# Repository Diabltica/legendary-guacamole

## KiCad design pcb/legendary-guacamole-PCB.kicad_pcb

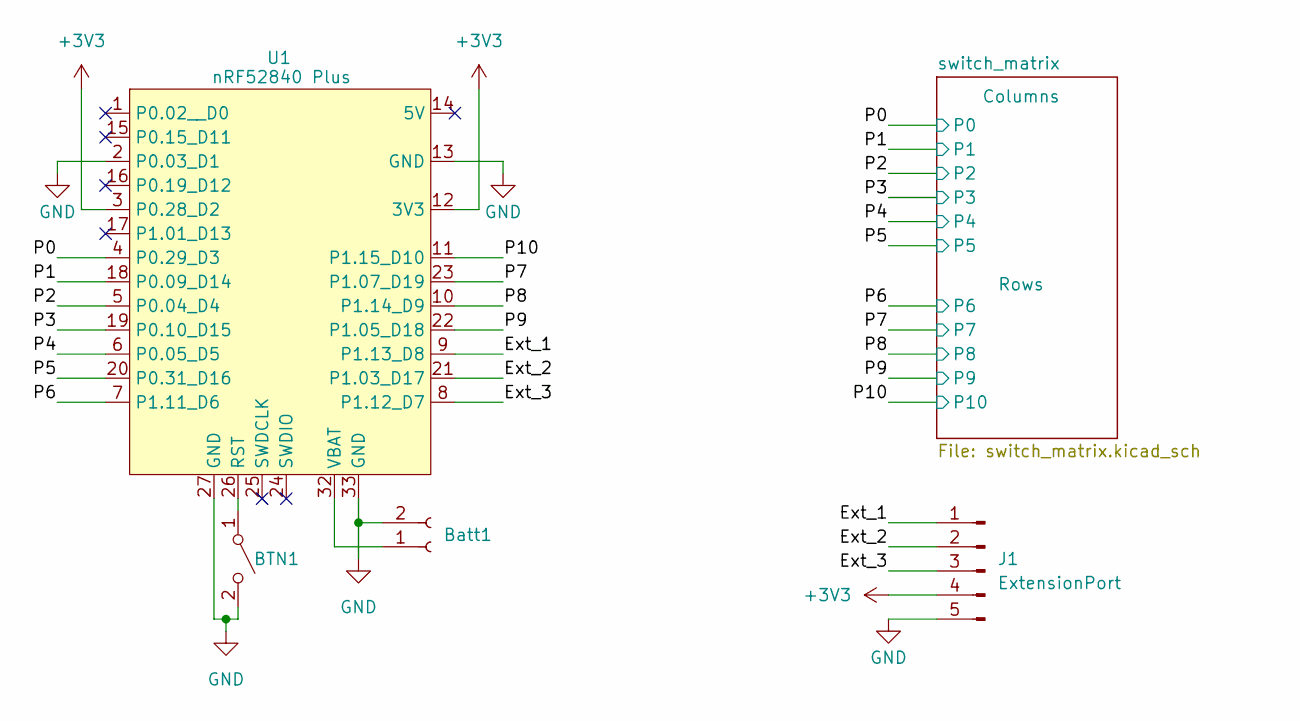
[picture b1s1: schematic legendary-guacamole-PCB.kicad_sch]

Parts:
BTN1: EVPBT5A4A000
Batt1: battery_connector_jst_ph_2
J1: ExtensionPort; PinHeader_1x05_P2.54mm_Vertical
U1: nRF52840 Plus; XIAO-nRF52840-Plus-SMD

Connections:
+3V3: J1.4, U1.3 (P0.28_D2), U1.12 (3V3); also elsewhere on the board
/Ext_1: J1.1, U1.9 (P1.13_D8); also elsewhere on the board
/Ext_2: J1.2, U1.21 (P1.03_D17); also elsewhere on the board
/Ext_3: J1.3, U1.8 (P1.12_D7); also elsewhere on the board
BAT_P: Batt1.1, U1.32 (VBAT); also elsewhere on the board
GND: BTN1.2 (B), Batt1.2, J1.5, U1.2 (P0.03_D1), U1.13 (GND), U1.27 (GND), U1.33 (GND); also elsewhere on the board
unnamed 8: BTN1.1 (A), U1.26 (RST); also elsewhere on the board
P0: U1.4 (P0.29_D3); also elsewhere on the board
P1: U1.18 (P0.09_D14); also elsewhere on the board
P2: U1.5 (P0.04_D4); also elsewhere on the board
P3: U1.19 (P0.10_D15); also elsewhere on the board
P4: U1.6 (P0.05_D5); also elsewhere on the board
P5: U1.20 (P0.31_D16); also elsewhere on the board
P6: U1.7 (P1.11_D6); also elsewhere on the board
P7: U1.23 (P1.07_D19); also elsewhere on the board
P8: U1.10 (P1.14_D9); also elsewhere on the board
P9: U1.22 (P1.05_D18); also elsewhere on the board
P10: U1.11 (P1.15_D10); also elsewhere on the board

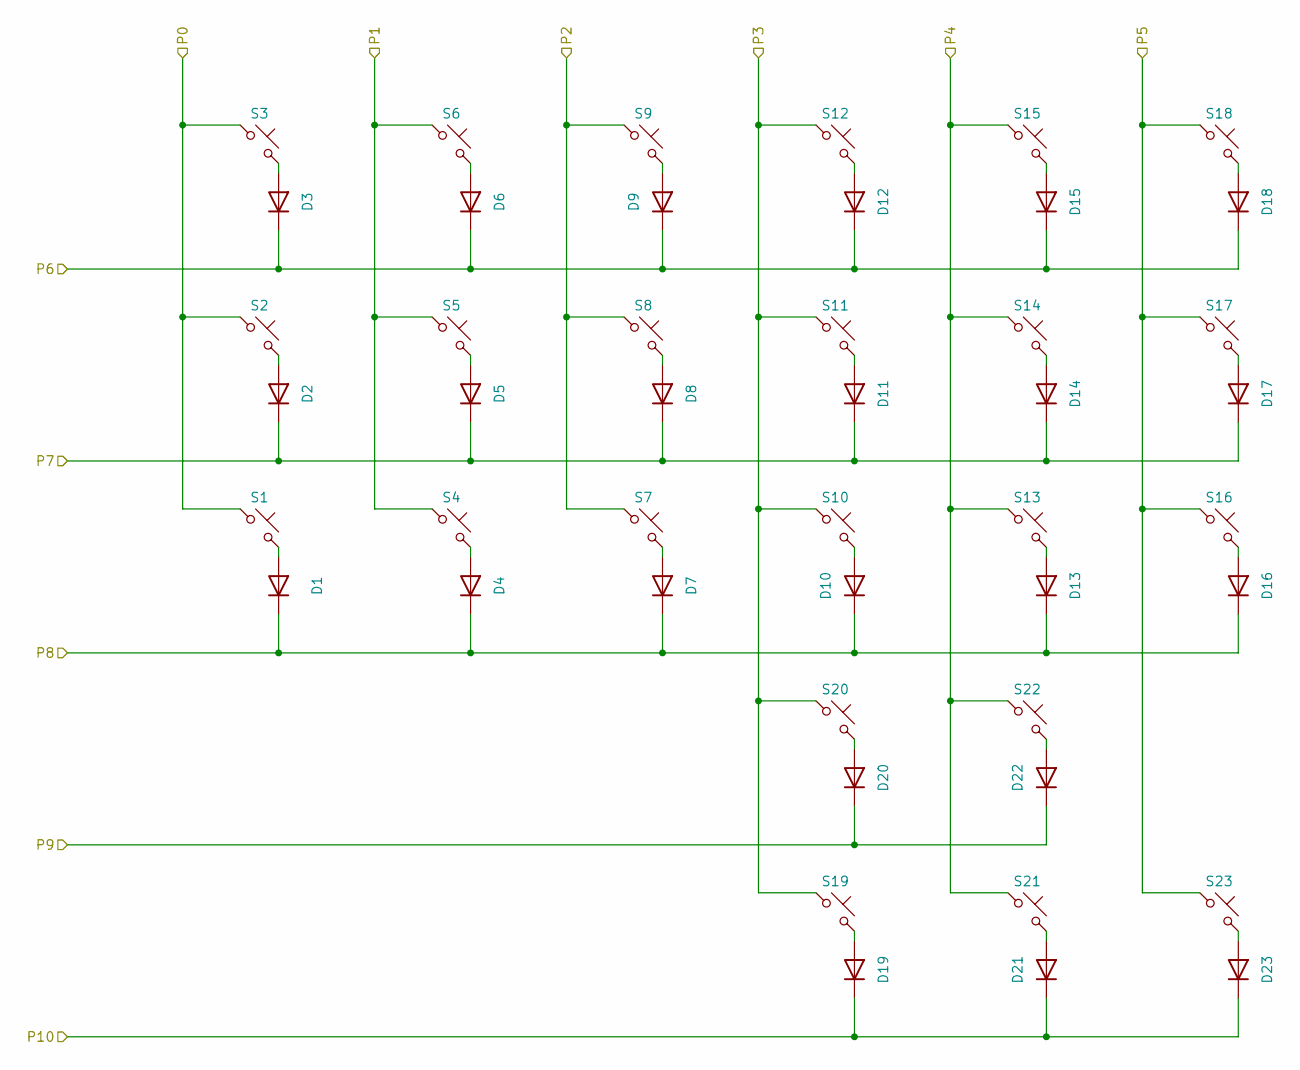
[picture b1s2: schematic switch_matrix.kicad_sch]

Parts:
D1, D2, D3, D4, D5, D6, D7, D8, D9, D10, D11, D12, D13, D14, D15, D16, D17, D18, D19, D20, D21, D22, D23: D_SOD-123
S1, S2, S3, S4, S5, S6, S7, S8, S9, S10, S11, S12, S13, S14, S15, S16, S17, S18, S19, S20, S21, S22, S23: (no value)

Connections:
P0: S1.1, S2.1, S3.1; also elsewhere on the board
P1: S4.1, S5.1, S6.1; also elsewhere on the board
P2: S7.1, S8.1, S9.1; also elsewhere on the board
P3: S10.1, S11.1, S12.1, S19.1, S20.1; also elsewhere on the board
P4: S13.1, S14.1, S15.1, S21.1, S22.1; also elsewhere on the board
P5: S16.1, S17.1, S18.1, S23.1; also elsewhere on the board
P6: D3.1 (K), D6.1 (K), D9.1 (K), D12.1 (K), D15.1 (K), D18.1 (K); also elsewhere on the board
P7: D2.1 (K), D5.1 (K), D8.1 (K), D11.1 (K), D14.1 (K), D17.1 (K); also elsewhere on the board
P8: D1.1 (K), D4.1 (K), D7.1 (K), D10.1 (K), D13.1 (K), D16.1 (K); also elsewhere on the board
P9: D20.1 (K), D22.1 (K); also elsewhere on the board
P10: D19.1 (K), D21.1 (K), D23.1 (K); also elsewhere on the board
index_bottom: D13.2 (A), S13.2
index_home: D14.2 (A), S14.2
index_top: D15.2 (A), S15.2
inner_bottom: D16.2 (A), S16.2
inner_home: D17.2 (A), S17.2
inner_top: D18.2 (A), S18.2
middle_bottom: D10.2 (A), S10.2
middle_home: D11.2 (A), S11.2
middle_top: D12.2 (A), S12.2
outer_bottom: D1.2 (A), S1.2
outer_home: D2.2 (A), S2.2
outer_top: D3.2 (A), S3.2
pinky_bottom: D4.2 (A), S4.2
pinky_home: D5.2 (A), S5.2
pinky_top: D6.2 (A), S6.2
ring_bottom: D7.2 (A), S7.2
ring_home: D8.2 (A), S8.2
ring_top: D9.2 (A), S9.2
thumb_1_row_0: D19.2 (A), S19.2
thumb_1_row_1: D20.2 (A), S20.2
thumb_2_row_0: D21.2 (A), S21.2
thumb_2_row_1: D22.2 (A), S22.2
thumb_3_row_0: D23.2 (A), S23.2

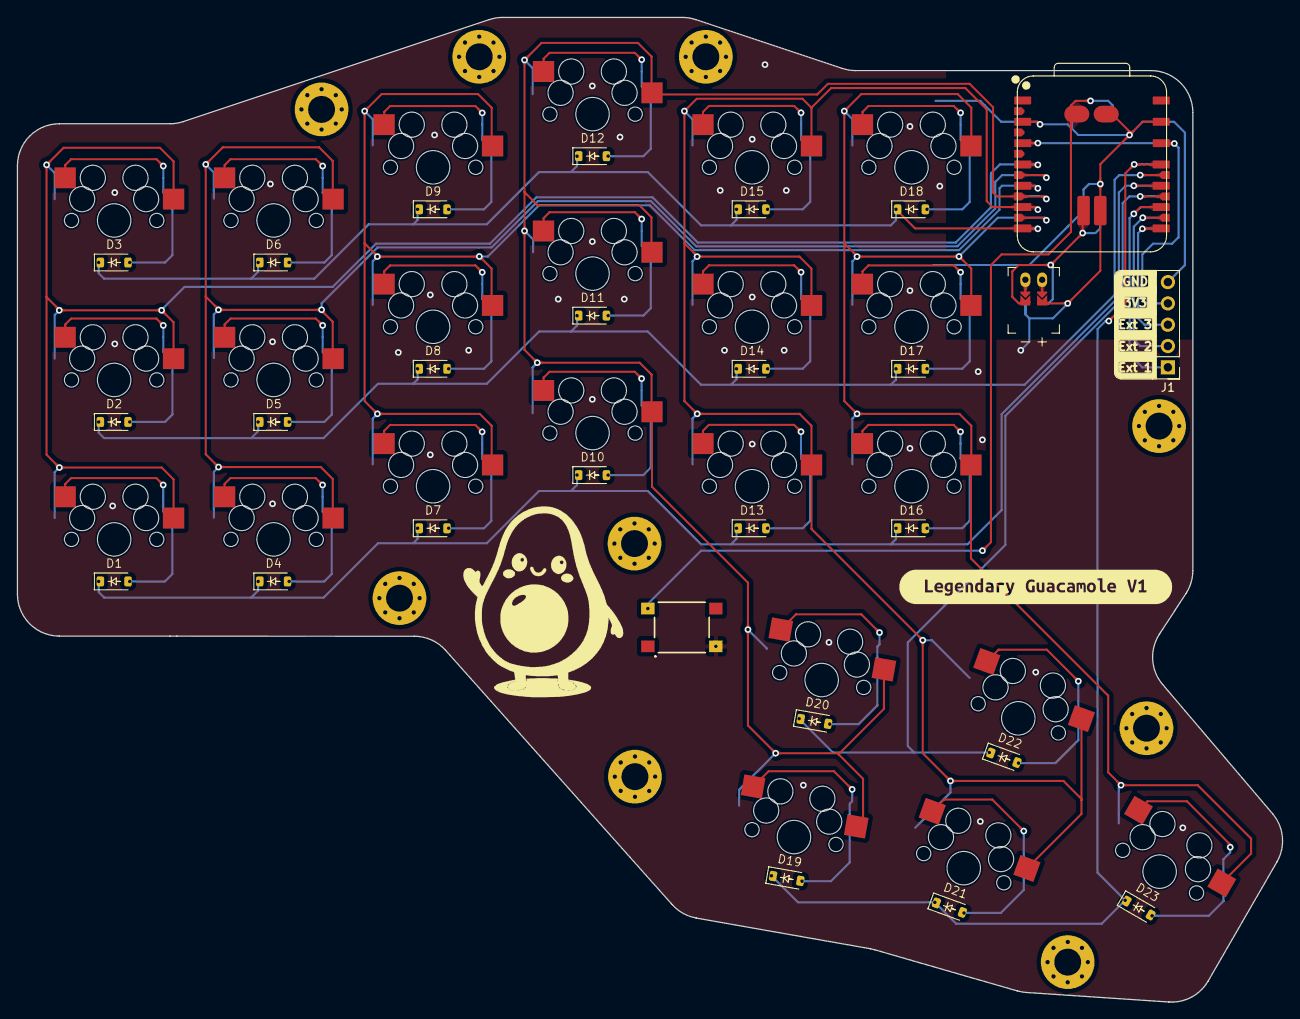
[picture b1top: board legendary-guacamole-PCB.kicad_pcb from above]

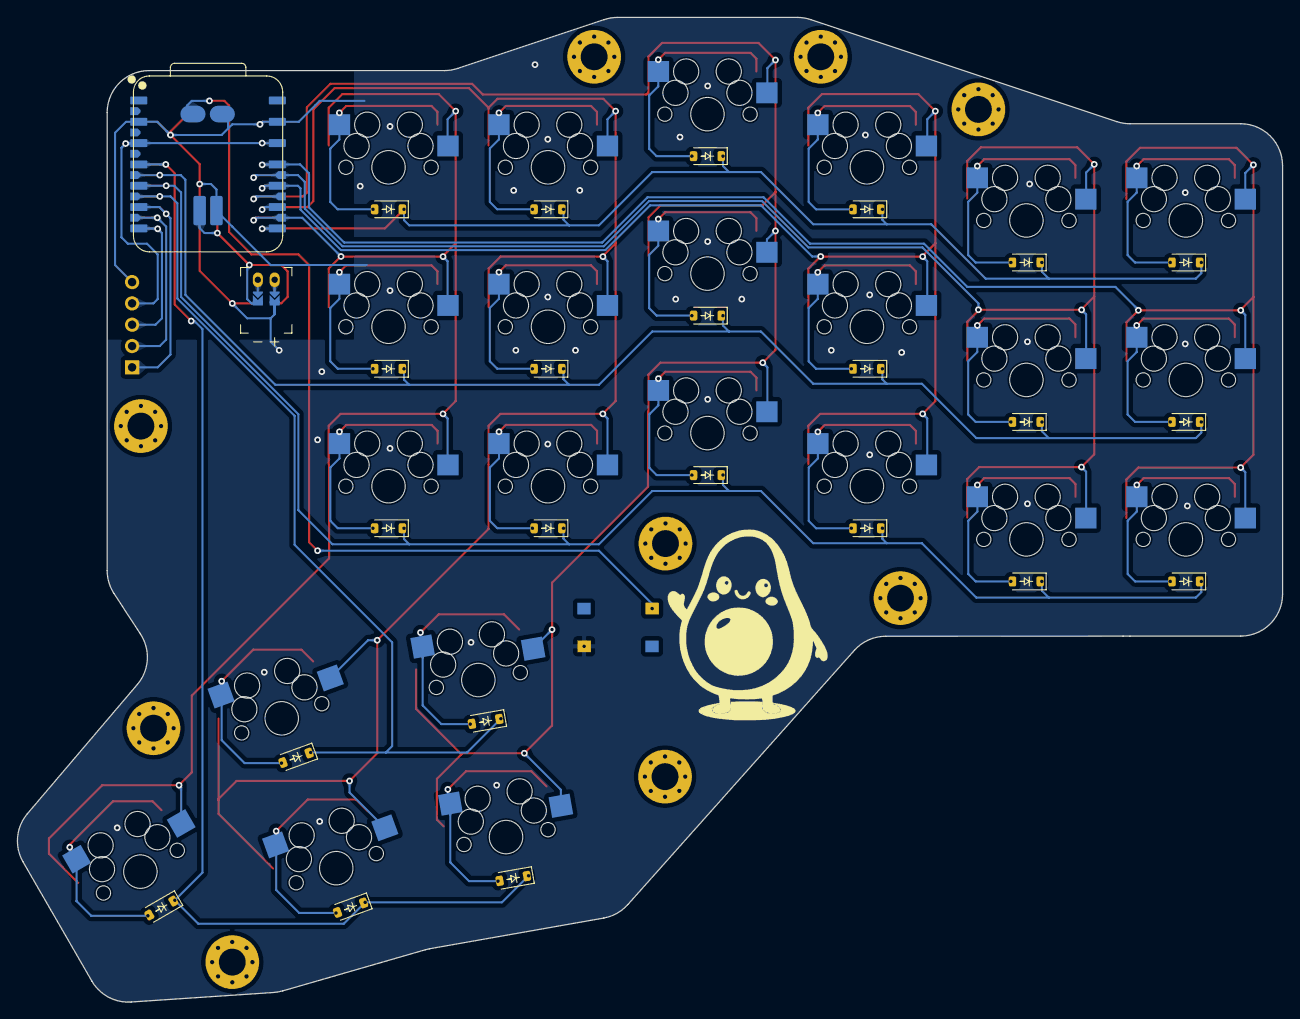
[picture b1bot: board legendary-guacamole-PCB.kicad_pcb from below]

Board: 2 copper layers, 150.7 x 117.3 mm, 52 parts (2 on the bottom side), 43 nets.

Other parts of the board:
JST1: JST
U1#2: nRF52840 Plus; XIAO-nRF52840-Plus-SMD
kibuzzard-69750C78: G***; kibuzzard-69750C78

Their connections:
+3V3: U1#2.3 (P0.28_D2), U1#2.12 (3V3); also elsewhere on the board
/Ext_1: U1#2.6 (P0.05_D5); also elsewhere on the board
/Ext_2: U1#2.20 (P0.31_D16); also elsewhere on the board
/Ext_3: U1#2.7 (P1.11_D6); also elsewhere on the board
BAT_P: JST1.1, U1#2.32 (VBAT); also elsewhere on the board
GND: JST1.2, U1#2.2 (P0.03_D1), U1#2.13 (GND), U1#2.27 (GND), U1#2.33 (GND); also elsewhere on the board
JST1_1: JST1.11, JST1.21, JST1.31
JST1_2: JST1.12, JST1.22, JST1.32
unnamed 8: U1#2.26 (RST); also elsewhere on the board
P0: U1#2.11 (P1.15_D10); also elsewhere on the board
P1: U1#2.23 (P1.07_D19); also elsewhere on the board
P2: U1#2.10 (P1.14_D9); also elsewhere on the board
P3: U1#2.22 (P1.05_D18); also elsewhere on the board
P4: U1#2.9 (P1.13_D8); also elsewhere on the board
P5: U1#2.21 (P1.03_D17); also elsewhere on the board
P6: U1#2.8 (P1.12_D7); also elsewhere on the board
P7: U1#2.18 (P0.09_D14); also elsewhere on the board
P8: U1#2.5 (P0.04_D4); also elsewhere on the board
P9: U1#2.19 (P0.10_D15); also elsewhere on the board
P10: U1#2.4 (P0.29_D3); also elsewhere on the board

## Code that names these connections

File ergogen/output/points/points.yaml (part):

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        autobind: 10
        skip: false
        asym: both
        colrow: pinky_bottom
        name: matrix_pinky_bottom
        column_net: P1
        row_net: P8
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        autobind: 10
        skip: false
        asym: both
        colrow: pinky_home
        name: matrix_pinky_home
        column_net: P1
        row_net: P7
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        autobind: 10
        skip: false
        asym: both
        colrow: pinky_top
        name: matrix_pinky_top
        column_net: P1
        row_net: P6
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
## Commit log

2025-04-20 first ergogen draft
2025-04-22 add thumb cluster wip
2025-04-26 final layout
2025-04-26 start adding footpprint
2025-05-03 add gitignore for kicad project
2025-05-03 forget to commit
2026-01-21 final key layout
2026-01-21 update pcb with new key layout
2026-01-21 fix diff between updated pcb and schematic
2026-01-23 add 3dmodel to pcb, first routing wip
2026-01-24 finish pcb routing, generate fabrication file and bom
2026-01-25 fix pcb (update sw footprint), start case design
2026-01-25 finished case
2026-03-08 update case and reorganize
2026-03-08 add zmk config file and workflow
2026-03-08 update keymap
2026-03-09 add layer change behaviour
2026-03-09 change layer key for test purpose
2026-03-11 add bt layer
2026-03-11 fix bt keymap
2026-03-11 cleanup file
2026-03-12 try combo
2026-03-12 move to macro
2026-03-12 test new macro
2026-03-12 remove macro and add combo
2026-03-12 fix a grave
2026-03-12 remove old macro ref
2026-03-12 fix keymap
2026-03-12 fix symbole layer and remove accent layer
2026-03-12 fix symbole layer
2026-03-12 change layer number
2026-03-12 fix typo
2026-03-12 move win key and add ^ key
2026-03-12 inverse LBKT and win key
2026-03-13 limit combo to layer 0
2026-03-16 update keyboard conf
2026-03-17 add combo for ampersand and escape
2026-03-17 replace escape with del on left side
2026-03-18 shift left symbol one column
2026-04-26 add reset and azerty layer for gaming
2026-04-26 add bracket
2026-04-26 add escape key :)
